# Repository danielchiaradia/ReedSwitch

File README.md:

# ReedSwitch
Simple Door/Window contact with low quiescence current of around 5µA (according to my cheap multimeter ...). There is quite some power loss on the ESP development board caused by the regulator, serial converter and other components. However, it will only be powered for a short amount time, so it's not worth going the hard naked ESP way here.

# BOM
- ESP01
- Attiny85
- LiFePO4 Battery
- 2 x 3K3 Ohm resistor
- 410 µF capacitor
- Reed Switch with two terminals or alternatively a normally closed reed switch.
- 1xP-Channel MOSFET (e.g.NDP6020P)

# How it works
The attiny will be turned on by the reed switch and then turns the ESP via the MOSFET on. The ESP sends the current state of the reed switch to a REST service. After sending the data, the ESP signals to the attiny to turn of the power.

# Quiescence current
Around 5-10 µA with closed reed switch. Open switch will cause around 20-30 µA current (probably the closed terminal draws some current)

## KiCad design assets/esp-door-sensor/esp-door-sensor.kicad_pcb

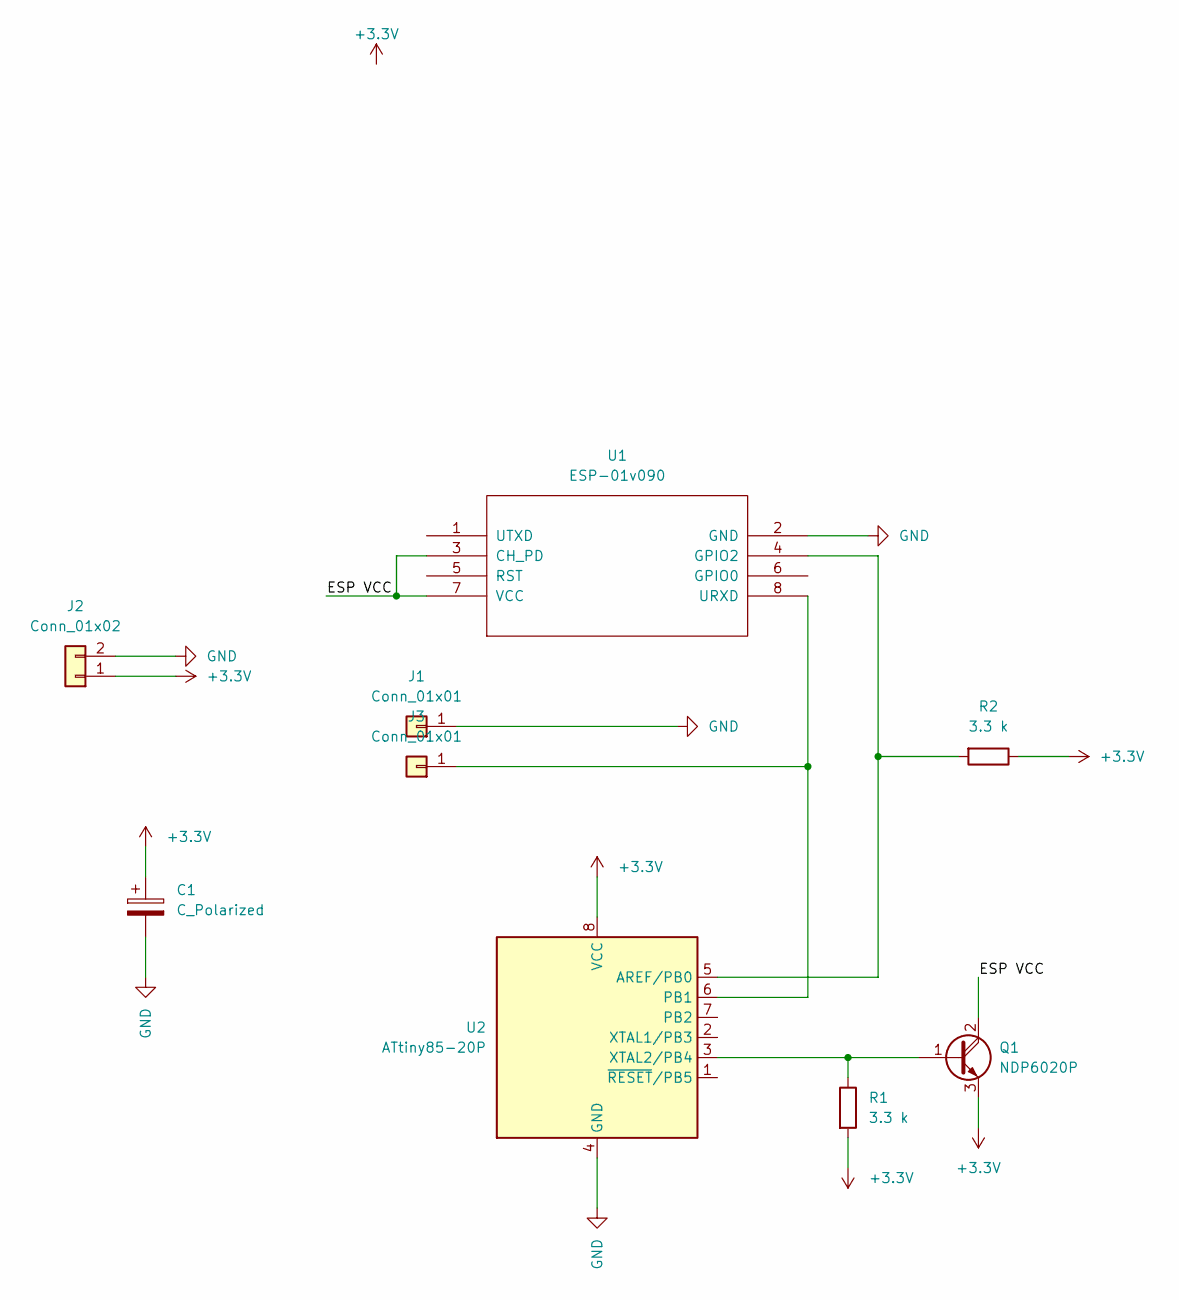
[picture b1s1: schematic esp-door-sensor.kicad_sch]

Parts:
C1: C_Polarized; CP_Radial_D6.3mm_P2.50mm
J1, J3: Conn_01x01; SolderWire-0.75sqmm_1x01_D1.25mm_OD2.3mm
J2: Conn_01x02; SolderWire-0.75sqmm_1x02_P7mm_D1.25mm_OD3.5mm
Q1: NDP6020P; TO-220-3_Vertical
R1, R2: 3.3 k; R_Axial_DIN0207_L6.3mm_D2.5mm_P7.62mm_Horizontal
U1: ESP-01v090; ESP-01
U2: ATtiny85-20P; DIP-8_W7.62mm

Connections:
+3.3V: C1.1, J2.1, Q1.3 (E), R1.2, R2.1, U2.8 (VCC)
/ESP VCC: Q1.2 (C), U1.3 (CH_PD), U1.7 (VCC)
GND: C1.2, J1.1, J2.2, U1.2 (GND), U2.4 (GND)
unnamed: Q1.1 (B), R1.1, U2.3 (XTAL2/PB4)
unnamed: R2.2, U1.4 (GPIO2), U2.5 (AREF/PB0)
unnamed: J3.1, U1.8 (URXD), U2.6 (PB1)

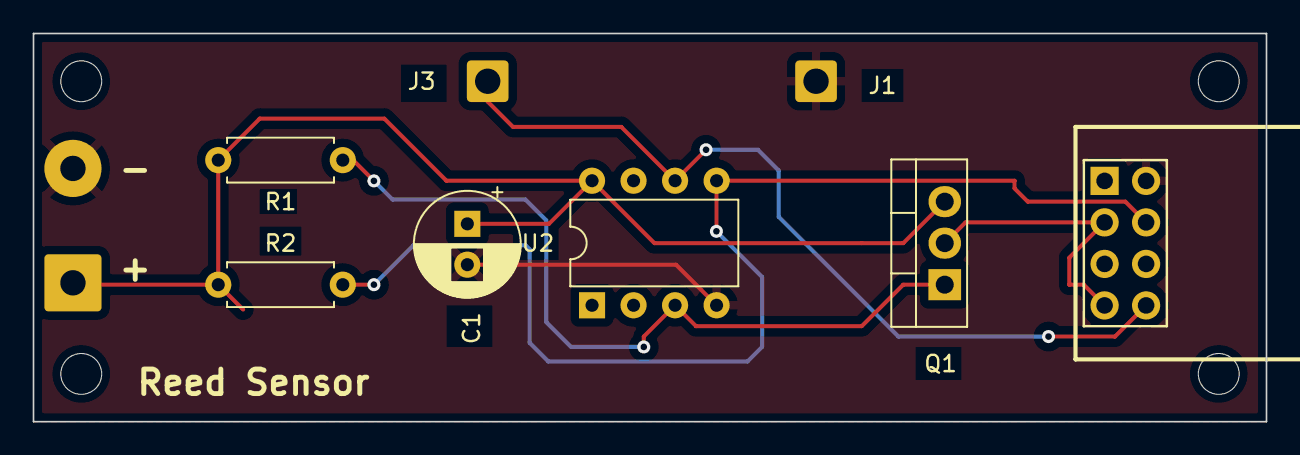
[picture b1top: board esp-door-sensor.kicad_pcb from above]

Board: 2 copper layers, 75.4 x 23.7 mm, 9 parts (0 on the bottom side), 6 nets.

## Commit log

2021-12-04 Normaly closed switch
2021-12-11 Images and Fusion360 file
2023-01-05 PCB finalized
